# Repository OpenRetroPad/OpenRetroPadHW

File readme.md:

OpenRetroPad Hardware
=====================

This repository holds some hardware designs to support [OpenRetroPad](https://github.com/OpenRetroPad/OpenRetroPad) software development. For more information, see specific hardware directories.

* [ATmega32u4](ATmega32u4)

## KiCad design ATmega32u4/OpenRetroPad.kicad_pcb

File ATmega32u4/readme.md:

# OpenRetroPadHW - ATmega32u4

* [Schematic](outputs/OpenRetroPad.pdf)
* [Layout/Assembly](outputs/OpenRetroPad-Assembly.pdf)
* [PCB Top](outputs/OpenRetroPad-top.png)
* [PCB Bottom](outputs/OpenRetroPad-bottom.png)

## Overview

This board is based around an [ATmega32u4](https://www.microchip.com/en-us/product/ATmega32U4) which is commonly seen on the official [Arduino Micro](https://docs.arduino.cc/hardware/micro) and [Leonardo](https://docs.arduino.cc/hardware/leonardo) boards. They are also on a fair number of third party Arduino compatible boards known as 'Pro Micro' (e.g. sparkfun's [Pro Micro](https://www.sparkfun.com/products/12640)).

The current design includes two USB-C plugs of which both can be used for programming, J2 over a CH330N/CH340N USB-UART serial connection or J1 over USB DFU.

A 2x4 female 2.54mm/0.1in header is also available for an nRF24L01 wireless transceiver module.

Controllers can be connected via a male DB25 mounted on the PCB. The recommended way of doing this with off the shelf controllers is by splicing cheap extension cables with a DB25 connector.

The PCB has been designed to be manufactured and assembled with [JLCPCB](https://jlcpcb.com/). Cost was part of the decision to use this company, but also the easy integration with their sister company [LCSC](https://www.lcsc.com/) which makes the ordering process for the BOM relatively painless (providing you are using parts available in their library).

## Software

[KiCad](https://www.kicad.org/) was used to design the schematic and PCB. Version 6 has come leaps and bounds and is a very capable ecad software compared to commercial offerings.

The schematic uses a heirachical design and [vector buses](https://docs.kicad.org/6.0/en/eeschema/eeschema.html#bus-connections) extensively. To view the pins for each vector bus, select the _Tools_ -> _Bus Definitions_ menu in the schematic editor.

Output PNG files were generated using the following linux commands,
```
pdftoppm OpenRetroPad.pdf png/OpenRetroPad.pdf -png -r 600
pdftoppm OpenRetroPad-Assembly.pdf png/OpenRetroPad-Assembly.pdf -png -r 600
pngquant --ext .png -f --skip-if-larger --speed 1 --strip png/*.png
```

### Plugins

* [Board2Pdf](https://gitlab.com/dennevi/Board2Pdf) has been used to generate the assembly PDF from the PCB layers. COlours have been adjusted to roughly match the default KiCad 6 theme colours for copper, silkscreen etc.

* [KiCAD JLCPCB tools](https://github.com/bouni/kicad-jlcpcb-tools) has been used to simplify the part selection for the BOM and generate assembly outputs for the manufacturer.

## Hardware Design

#### Mechanical

M3 (3.2mm diameter) mounting holes have been added to the corner of the board. These holes have exposed copper for screws, but are not grounded. For precise measurements, see the assembly PDF above.

TODO:
* Consider grounding mounting hole pads

#### Power

The board is powered by either USB-C connector, which have been separated from each other, and provided with some basic reverse polarity protection, with a schottky diode on each VBUS connection. This will mean an approximate 0.3V drop on the 5V line but that should be more than fine for this purpose. The microcontroller still runs acceptably fine above 4.5V at 16MHz.

Assumptions have been made that the 5V USB supply is relatively stable so for the digital supply only decoupling capacitors are used. However, a ferrite bead has also been used for filtering the two analog supply inputs.

A larger 'bulk' 10u capacitor has been added near the each USB connector supply, and each CC pin has been pulled down with 5.1k resistors as per the USB spec Rd pulldown resistor for basic USB power. The CC pins have been routed to the microcontroller for the data connector to measure the voltage divider and power available.

A power LED is used on the 5V line. This LED can be physically disabled by cutting the JP1 solder bridge.

TODO:
* Test if both USB-C connectors can be used simultaneously with the schottky diodes
* Potentially add ferrite bead on each USB supply
* Fuses on inputs?
* Consider filter on USB shield - potentially small cap and large resistor, or even a ferrite bead

#### Microcontroller

The microcontroller was initially based on microchip application mate [AN2519 - AVR Microcontroller Hardware Design Considerations (DS00002519)](https://ww1.microchip.com/downloads/en/Appnotes/AN2519-AVR-Microcontroller-Hardware-Design-Considerations-00002519B.pdf).

The [quad flat package](https://en.wikipedia.org/wiki/Quad_flat_package) was used for this microcontroller, as opposed to the [quad flat no-lead package](https://en.wikipedia.org/wiki/Flat_no-leads_package). Throughout the covid chip shortage, the QFP part were harder to source and more expensive, but have now come back down to reasonable levels.

##### Programming via USB DFU

The board can be programmed via UART, but some information is provided here for programming via USB DFU if any issues are encountered.

Bootloader uses [PC7](https://github.com/arduino/ArduinoCore-avr/blob/master/bootloaders/caterina/Caterina.h#L69) as output for led pulsing in hardware bootloader mode ( https://github.com/arduino/ArduinoCore-avr/blob/master/bootloaders/caterina/Caterina.c#L151 and https://github.com/arduino/ArduinoCore-avr/blob/master/bootloaders/caterina/Caterina.c#L95 ). This LED can otherwise be used in user code for status indication. TX (D5) and RX (B0) are also broken out for LED activity.

Switch 1 (labelled 'HWB') enters hardware bootloader mode. Switch 2 (labelled 'Reset') resets the microcontroller. To enter the hardware bootloader, in this order: press reset, press hwb, release reset, release hwb. HWB has weak pullup to not use bootloader on reset.

USB DFU mode as per http://ww1.microchip.com/downloads/en/DeviceDoc/doc7618.pdf

DFU drivers can be found in [FLIP](https://www.microchip.com/developmenttools/ProductDetails/flip)
Flip is not required to be installed unless uploading a .hex file manually

Flags to avrdude to upload: -c flip1 -p m32u4 -P usb
Flip is not required to be installed for avrdude to use the protocol.

#### UART

The CH330N/CH340N are interchangeable parts. Datasheet recommends not powering CH340 and MCU separately. Could cause issues when using TX/RX port for controllers.

TODO:
* Investigate powering separately, adding diode instead of resistors to RXD/TXD

#### I/O

The DB-25 male connector is connected as per the [wiring table here](https://github.com/openRetroPad/openRetroPad#wiring)

The 5V and 3.3V lines are both fused for protection.

Once the microcontroller is booted (a few milliseconds), the HWB button can be used as a user programmable button.

There are multiple LEDs on the board that can be used for I/O.

#### Wireless Transceiver

The original software had functionality for wireless connections using an nRF24L01 module. This board provides a header to plug in one of these modules. They don't appear to be "official" nordic semi modules in any capacity, but any module with the pinout matching the header (check the back side of the PCB) should work.

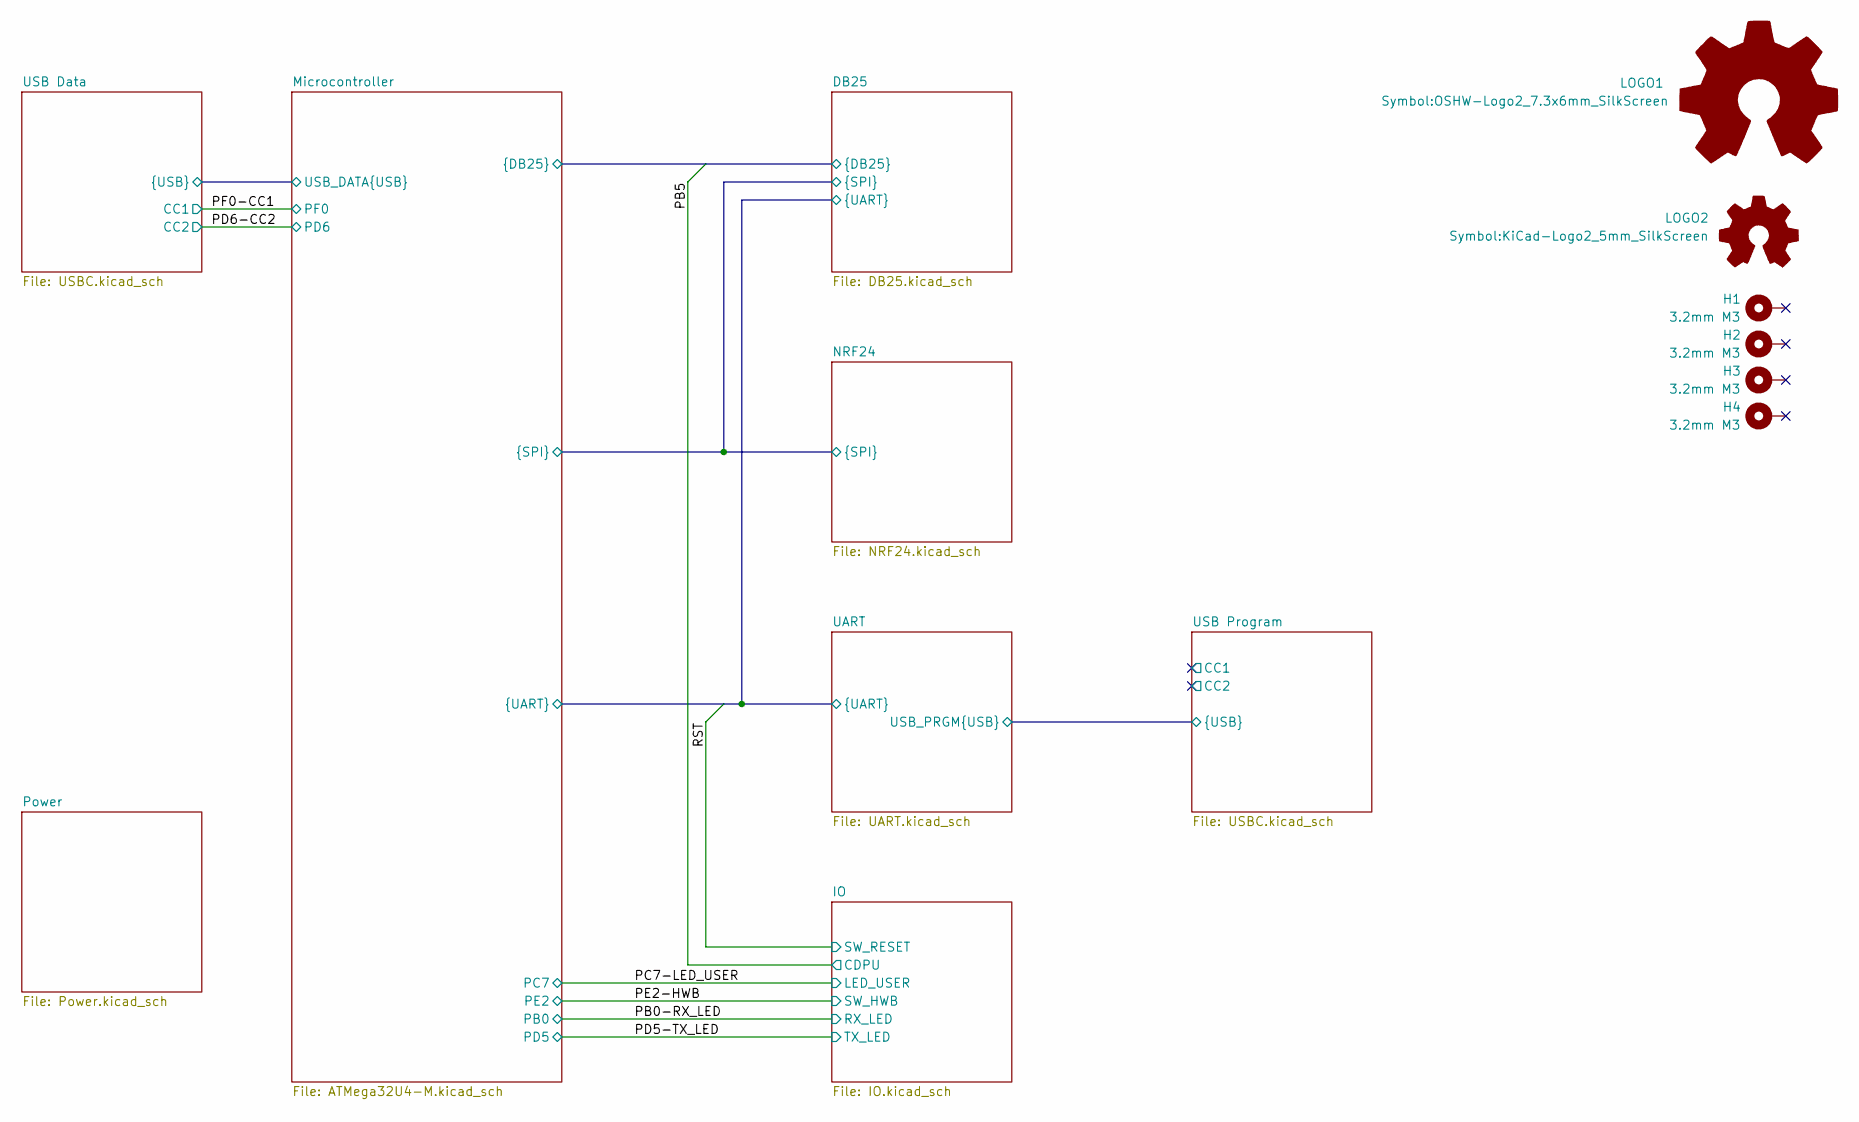
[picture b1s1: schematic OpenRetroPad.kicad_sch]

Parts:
H1, H2, H3, H4: 3.2mm M3; MountingHole_3.2mm_M3_Pad_Via
LOGO1: Logo_Open_Hardware_Large; OSHW-Logo2_7.3x6mm_SilkScreen
LOGO2: Logo_Open_Hardware_Small; KiCad-Logo2_5mm_SilkScreen

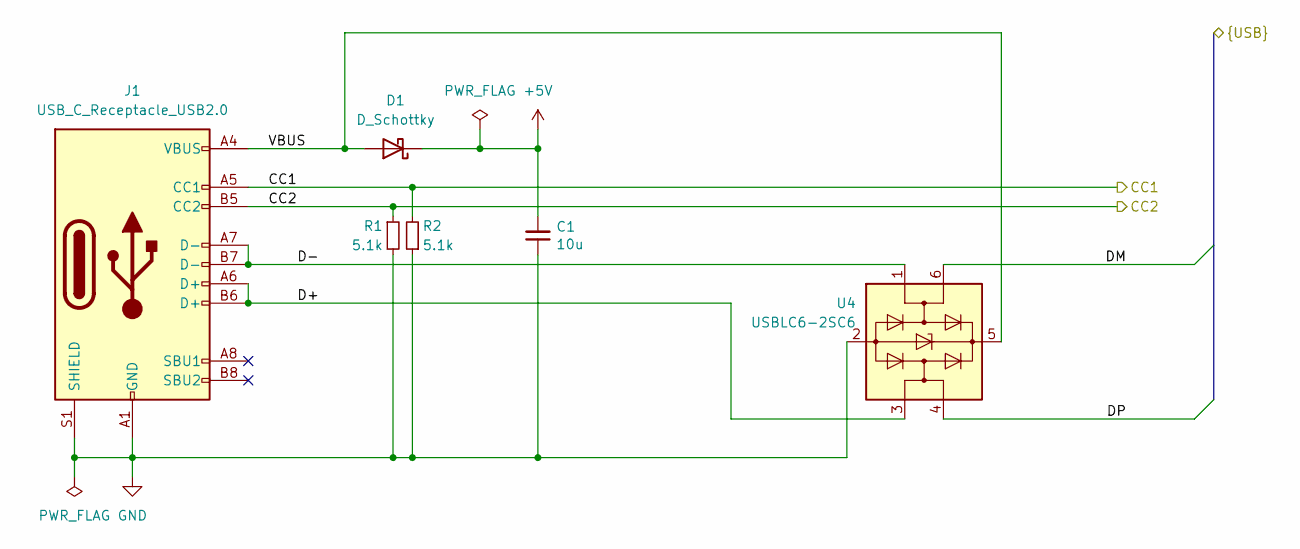
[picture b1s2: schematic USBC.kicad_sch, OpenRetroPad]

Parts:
C1: 10u; C_0805_2012Metric
D1: D_Schottky; D_SOD-323
J1: USB_C_Receptacle_USB2.0; USB_C_Receptacle_HRO_TYPE-C-31-M-12
R1, R2: 5.1k; R_0603_1608Metric
U4: USBLC6-2SC6; SOT-23-6

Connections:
+5V: C1.2, D1.1 (K); also elsewhere on the board
/Microcontroller/USB_DATA.DM: U4.6 (I/O1); also elsewhere on the board
/Microcontroller/USB_DATA.DP: U4.4 (I/O2); also elsewhere on the board
/PD6-CC2: J1.B5 (CC2), R1.1; also elsewhere on the board
/PF0-CC1: J1.A5 (CC1), R2.2; also elsewhere on the board
/USB Data/D+: J1.A6 (D+), J1.B6 (D+), U4.3 (I/O2)
/USB Data/D-: J1.A7 (D-), J1.B7 (D-), U4.1 (I/O1)
/USB Data/VBUS: D1.2 (A), J1.A4 (VBUS), J1.A9 (VBUS), J1.B4 (VBUS), J1.B9 (VBUS), U4.5 (VBUS)
GND: C1.1, J1.A1 (GND), J1.A12 (GND), J1.B1 (GND), J1.B12 (GND), J1.S1 (SHIELD), R1.2, R2.1, U4.2 (GND); also elsewhere on the board

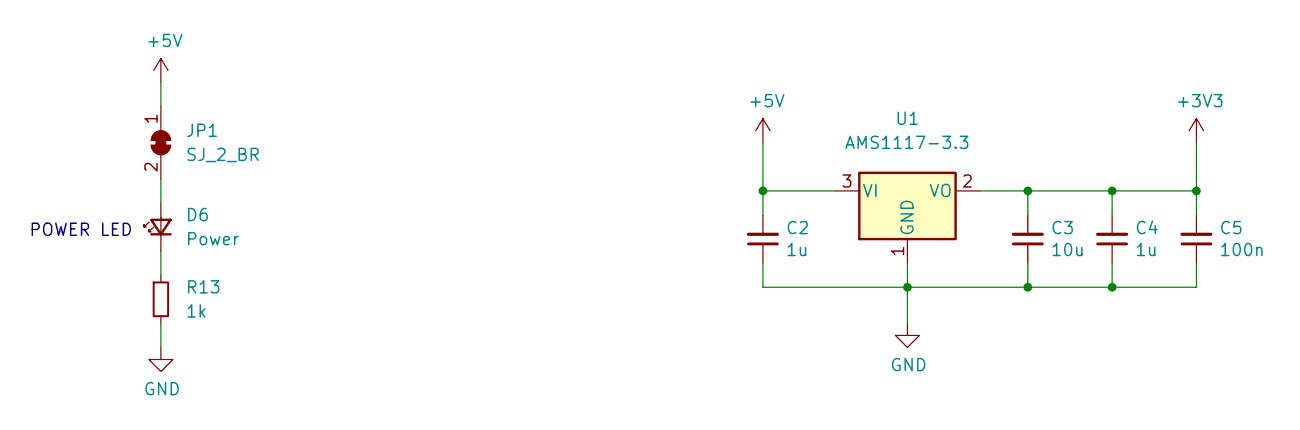
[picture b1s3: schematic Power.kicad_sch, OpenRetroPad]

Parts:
C2, C4: 1u; C_0603_1608Metric
C3: 10u; C_0805_2012Metric
C5: 100n; C_0603_1608Metric
D6: Power; LED_0603_1608Metric
JP1: SJ_2_BR; SolderJumper-2_P1.3mm_Bridged_RoundedPad1.0x1.5mm
R13: 1k; R_0603_1608Metric
U1: AMS1117-3.3; SOT-223-3_TabPin2

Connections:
+3V3: C3.2, C4.2, C5.2, U1.2 (VO); also elsewhere on the board
+5V: C2.2, JP1.1 (A), U1.3 (VI); also elsewhere on the board
GND: C2.1, C3.1, C4.1, C5.1, R13.2, U1.1 (GND); also elsewhere on the board
unnamed: D6.1 (K), R13.1
unnamed: D6.2 (A), JP1.2 (B)

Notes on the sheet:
POWER LED

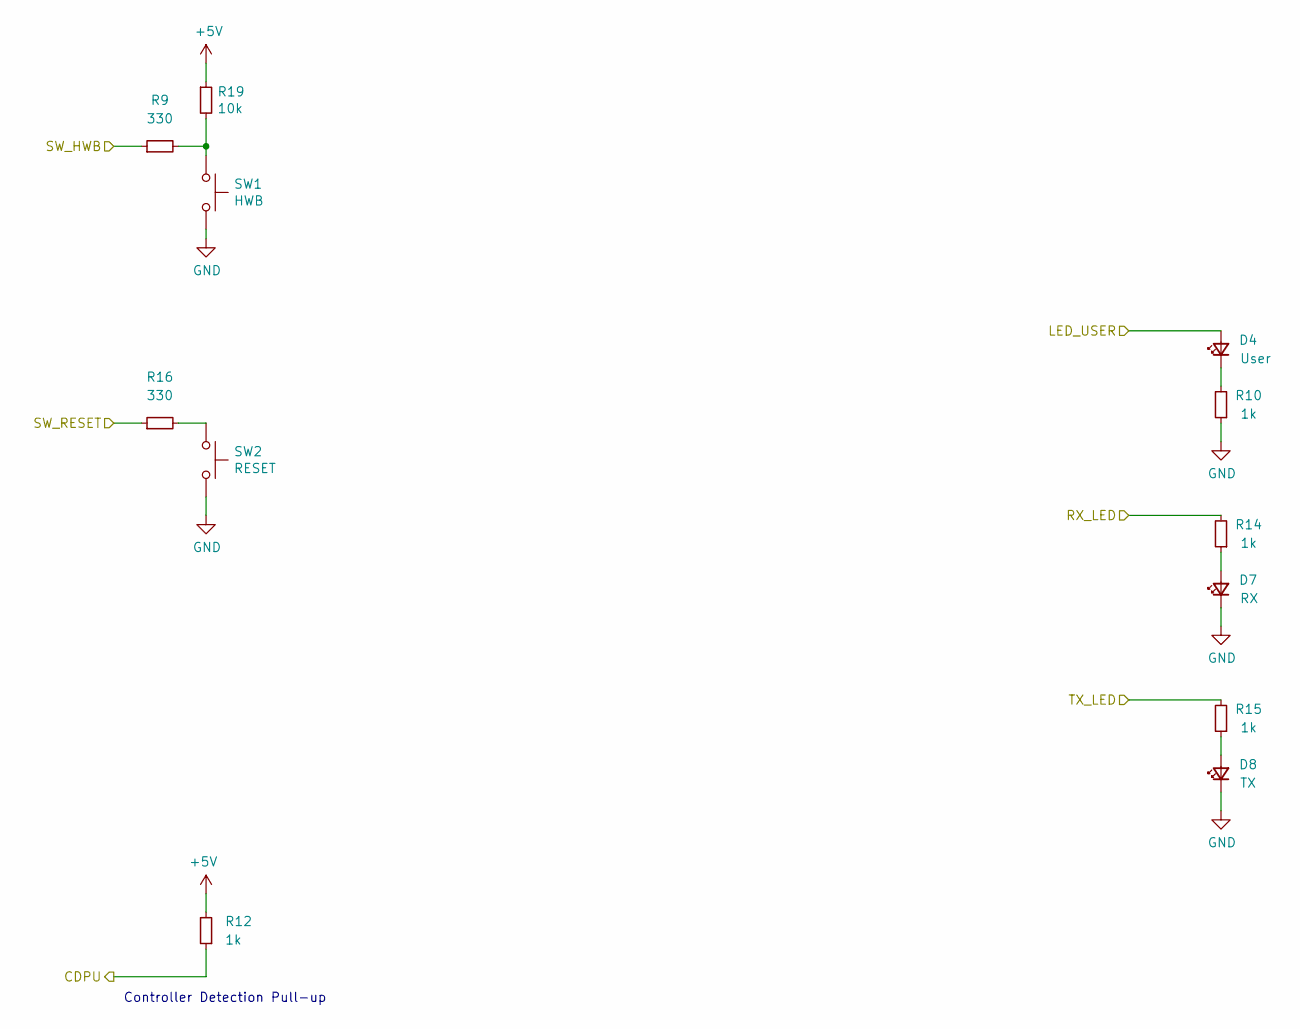
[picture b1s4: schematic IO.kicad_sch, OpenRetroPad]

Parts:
D4: User; LED_0603_1608Metric
D7: RX; LED_0603_1608Metric
D8: TX; LED_0603_1608Metric
R9, R16: 330; R_0603_1608Metric
R10, R12, R14, R15: 1k; R_0603_1608Metric
R19: 10k; R_0603_1608Metric
SW1: HWB; Alps_SKRK
SW2: RESET; Alps_SKRK

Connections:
+5V: R12.2, R19.1; also elsewhere on the board
/DB25/PB5: R12.1; also elsewhere on the board
/DB25/RST: R16.1; also elsewhere on the board
/PB0-RX_LED: R14.2; also elsewhere on the board
/PC7-LED_USER: D4.2 (A); also elsewhere on the board
/PD5-TX_LED: R15.2; also elsewhere on the board
/PE2-HWB: R9.1; also elsewhere on the board
GND: D7.1 (K), D8.1 (K), R10.1, SW1.2, SW2.2; also elsewhere on the board
unnamed: D4.1 (K), R10.2
unnamed: D7.2 (A), R14.1
unnamed: D8.2 (A), R15.1
unnamed: R16.2, SW2.1
unnamed: R9.2, R19.2, SW1.1

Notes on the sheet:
Controller Detection Pull-up

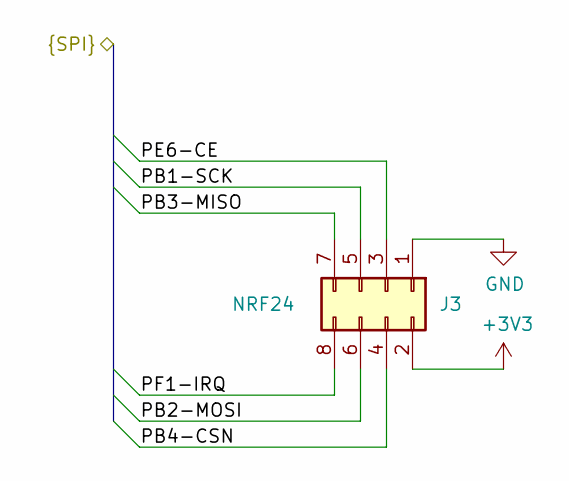
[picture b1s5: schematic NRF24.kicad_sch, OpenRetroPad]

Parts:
J3: NRF24; NRF24L01

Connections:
+3V3: J3.2; also elsewhere on the board
/DB25/PB1-SCK: J3.5; also elsewhere on the board
/DB25/PB2-MOSI: J3.6; also elsewhere on the board
/DB25/PB3-MISO: J3.7; also elsewhere on the board
/DB25/PB4-CSN: J3.4; also elsewhere on the board
/DB25/PE6-CE: J3.3; also elsewhere on the board
/DB25/PF1-IRQ: J3.8; also elsewhere on the board
GND: J3.1; also elsewhere on the board

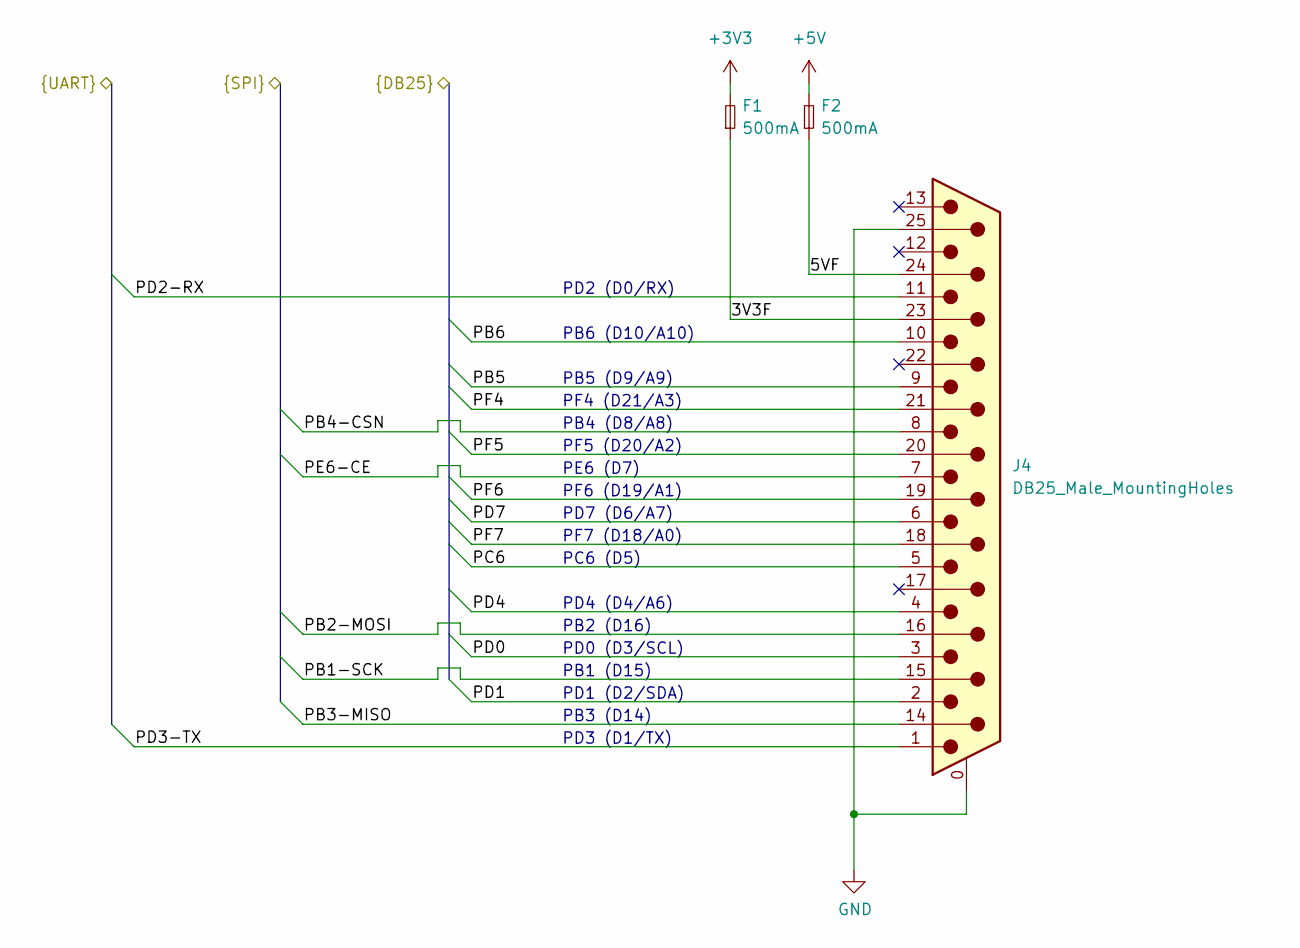
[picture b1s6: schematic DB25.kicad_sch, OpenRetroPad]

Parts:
F1, F2: 500mA; Fuse_0805_2012Metric
J4: DB25_Male_MountingHoles; DSUB-25_Male_Horizontal_P2.77x2.84mm_EdgePinOffset7.70mm_Ho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

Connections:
+3V3: F1.2; also elsewhere on the board
+5V: F2.2; also elsewhere on the board
/DB25/3V3F: F1.1, J4.23
/DB25/5VF: F2.1, J4.24
/DB25/PB1-SCK: J4.15; also elsewhere on the board
/DB25/PB2-MOSI: J4.16; also elsewhere on the board
/DB25/PB3-MISO: J4.14; also elsewhere on the board
/DB25/PB4-CSN: J4.8; also elsewhere on the board
/DB25/PB5: J4.9; also elsewhere on the board
/DB25/PB6: J4.10; also elsewhere on the board
/DB25/PC6: J4.5; also elsewhere on the board
/DB25/PD0: J4.3; also elsewhere on the board
/DB25/PD1: J4.2; also elsewhere on the board
/DB25/PD2-RX: J4.11; also elsewhere on the board
/DB25/PD3-TX: J4.1; also elsewhere on the board
/DB25/PD4: J4.4; also elsewhere on the board
/DB25/PD7: J4.6; also elsewhere on the board
/DB25/PE6-CE: J4.7; also elsewhere on the board
/DB25/PF4: J4.21; also elsewhere on the board
/DB25/PF5: J4.20; also elsewhere on the board
/DB25/PF6: J4.19; also elsewhere on the board
/DB25/PF7: J4.18; also elsewhere on the board
GND: J4.0 (PAD), J4.25; also elsewhere on the board

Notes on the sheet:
PD2 (D0/RX)
PD0 (D3/SCL)
PD4 (D4/A6)
PF6 (D19/A1)
PF4 (D21/A3)
PC6 (D5)
PB4 (D8/A8)
PB1 (D15)
PE6 (D7)
PB5 (D9/A9)
PD1 (D2/SDA)
PD3 (D1/TX)
PB3 (D14)
PF7 (D18/A0)
PB2 (D16)
PD7 (D6/A7)
PB6 (D10/A10)
PF5 (D20/A2)

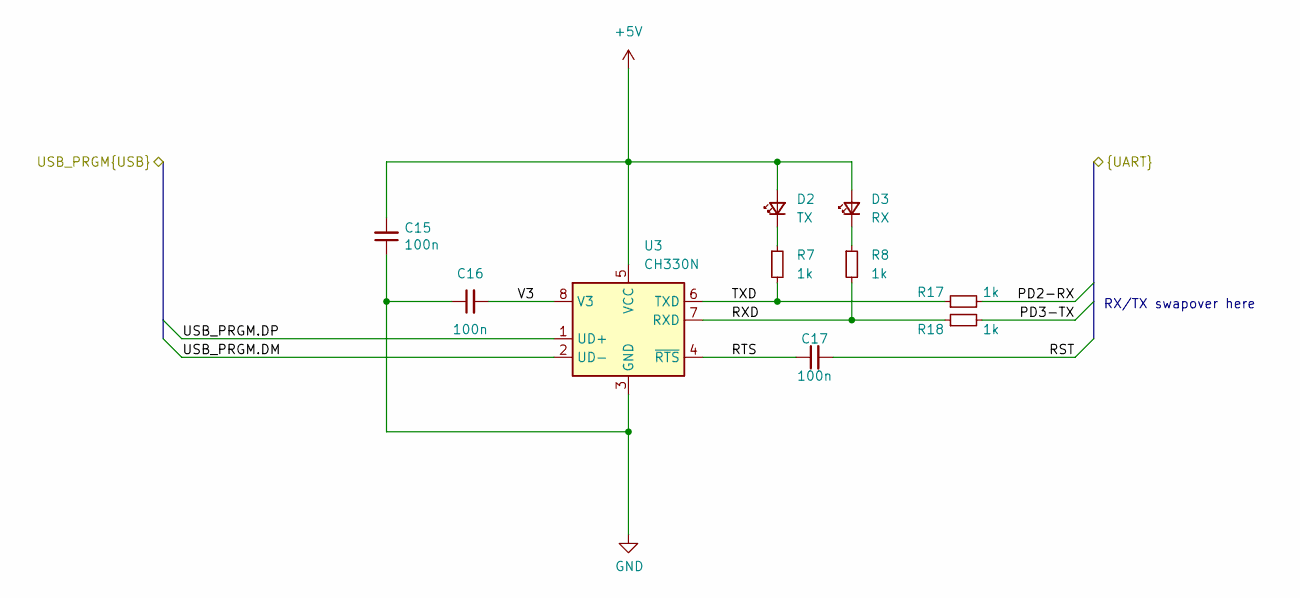
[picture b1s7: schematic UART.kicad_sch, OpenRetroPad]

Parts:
C15, C16, C17: 100n; C_0603_1608Metric
D2: TX; LED_0603_1608Metric
D3: RX; LED_0603_1608Metric
R7, R8, R17, R18: 1k; R_0603_1608Metric
U3: CH330N; SOIC-8_3.9x4.9mm_P1.27mm

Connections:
+5V: C15.2, D2.2 (A), D3.2 (A), U3.5 (VCC); also elsewhere on the board
/DB25/PD2-RX: R17.2; also elsewhere on the board
/DB25/PD3-TX: R18.2; also elsewhere on the board
/DB25/RST: C17.2; also elsewhere on the board
/UART/RTS: C17.1, U3.4 (~RTS)
/UART/RXD: R8.2, R18.1, U3.7 (RXD)
/UART/TXD: R7.2, R17.1, U3.6 (TXD)
/UART/USB_PRGM.DM: U3.2 (UD-); also elsewhere on the board
/UART/USB_PRGM.DP: U3.1 (UD+); also elsewhere on the board
/UART/V3: C16.2, U3.8 (V3)
GND: C15.1, C16.1, U3.3 (GND); also elsewhere on the board
unnamed: D2.1 (K), R7.1
unnamed: D3.1 (K), R8.1

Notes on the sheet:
RX/TX swapover here

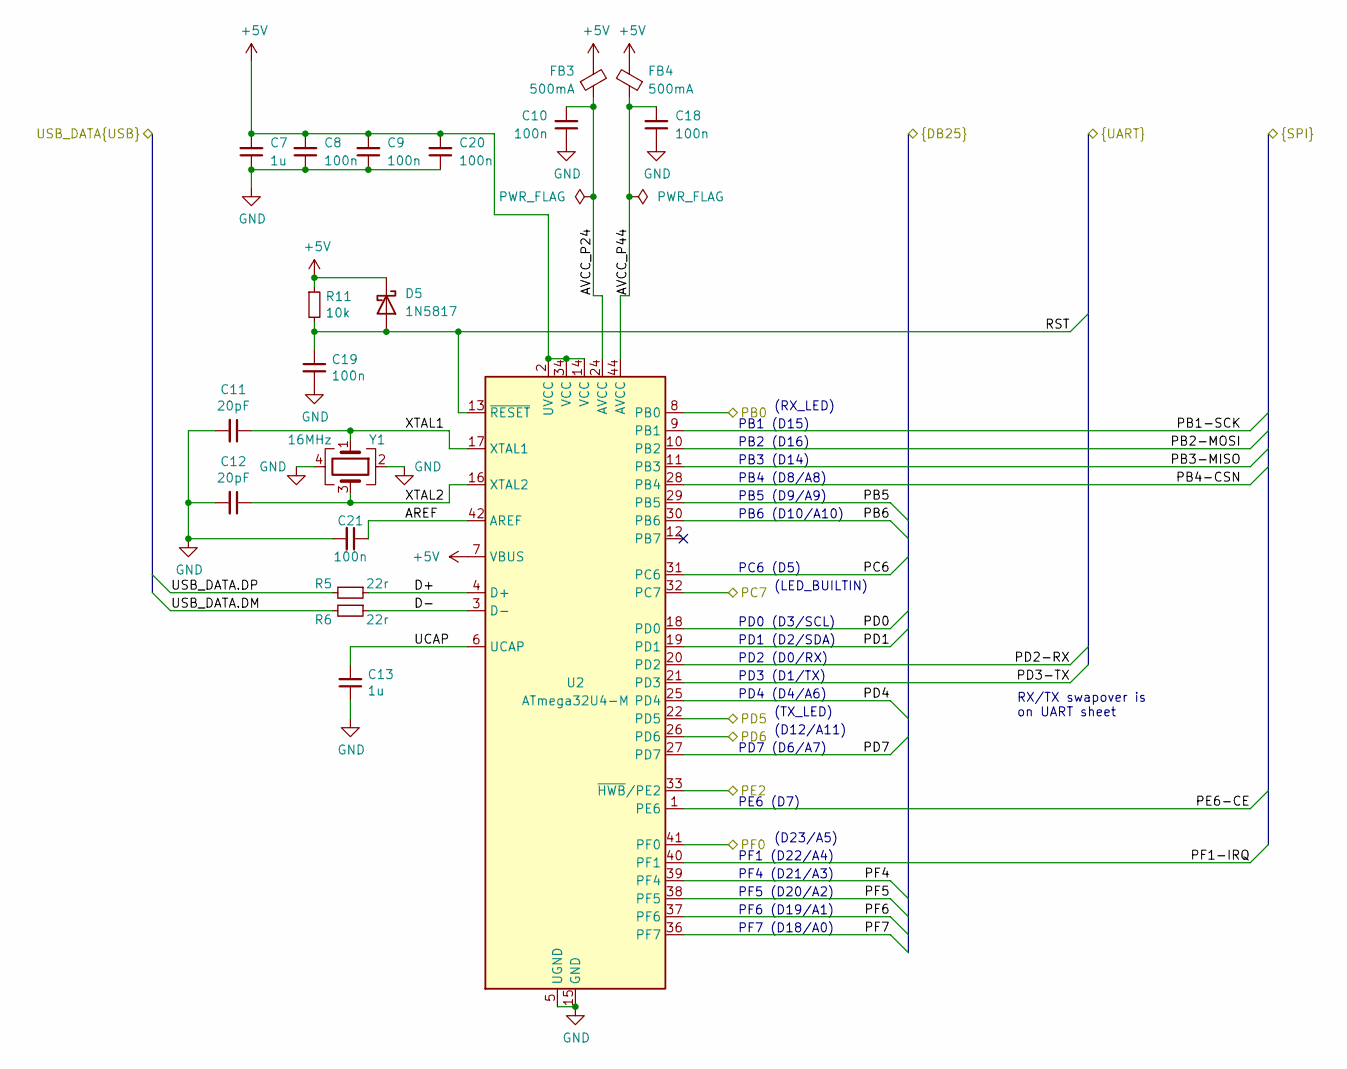
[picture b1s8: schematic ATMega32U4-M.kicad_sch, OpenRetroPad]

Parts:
C7, C13: 1u; C_0603_1608Metric
C8, C9, C10, C18, C19, C20, C21: 100n; C_0603_1608Metric
C11, C12: 20pF; C_0603_1608Metric
D5: 1N5817; D_SOD-323
FB3, FB4: 500mA; L_0603_1608Metric
R5, R6: 22r; R_0603_1608Metric
R11: 10k; R_0603_1608Metric
U2: ATmega32U4-M; TQFP-44_10x10mm_P0.8mm
Y1: 16MHz; Crystal_SMD_3225-4Pin_3.2x2.5mm

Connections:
+5V: C7.2, C8.2, C9.2, C20.2, D5.1 (K), FB3.2, FB4.2, R11.1, U2.2 (UVCC), U2.7 (VBUS), U2.14 (VCC), U2.34 (VCC); also elsewhere on the board
/DB25/PB1-SCK: U2.9 (PB1); also elsewhere on the board
/DB25/PB2-MOSI: U2.10 (PB2); also elsewhere on the board
/DB25/PB3-MISO: U2.11 (PB3); also elsewhere on the board
/DB25/PB4-CSN: U2.28 (PB4); also elsewhere on the board
/DB25/PB5: U2.29 (PB5); also elsewhere on the board
/DB25/PB6: U2.30 (PB6); also elsewhere on the board
/DB25/PC6: U2.31 (PC6); also elsewhere on the board
/DB25/PD0: U2.18 (PD0); also elsewhere on the board
/DB25/PD1: U2.19 (PD1); also elsewhere on the board
/DB25/PD2-RX: U2.20 (PD2); also elsewhere on the board
/DB25/PD3-TX: U2.21 (PD3); also elsewhere on the board
/DB25/PD4: U2.25 (PD4); also elsewhere on the board
/DB25/PD7: U2.27 (PD7); also elsewhere on the board
/DB25/PE6-CE: U2.1 (PE6); also elsewhere on the board
/DB25/PF1-IRQ: U2.40 (PF1); also elsewhere on the board
/DB25/PF4: U2.39 (PF4); also elsewhere on the board
/DB25/PF5: U2.38 (PF5); also elsewhere on the board
/DB25/PF6: U2.37 (PF6); also elsewhere on the board
/DB25/PF7: U2.36 (PF7); also elsewhere on the board
/DB25/RST: C19.1, D5.2 (A), R11.2, U2.13 (~RESET); also elsewhere on the board
/Microcontroller/AREF: C21.1, U2.42 (AREF)
/Microcontroller/AVCC_P24: C10.2, FB3.1, U2.24 (AVCC)
/Microcontroller/AVCC_P44: C18.2, FB4.1, U2.44 (AVCC)
/Microcontroller/D+: R5.1, U2.4 (D+)
/Microcontroller/D-: R6.1, U2.3 (D-)
/Microcontroller/UCAP: C13.2, U2.6 (UCAP)
/Microcontroller/USB_DATA.DM: R6.2; also elsewhere on the board
/Microcontroller/USB_DATA.DP: R5.2; also elsewhere on the board
/Microcontroller/XTAL1: C11.1, U2.17 (XTAL1), Y1.1
/Microcontroller/XTAL2: C12.1, U2.16 (XTAL2), Y1.3
/PB0-RX_LED: U2.8 (PB0); also elsewhere on the board
/PC7-LED_USER: U2.32 (PC7); also elsewhere on the board
/PD5-TX_LED: U2.22 (PD5); also elsewhere on the board
/PD6-CC2: U2.26 (PD6); also elsewhere on the board
/PE2-HWB: U2.33 (~HWB/PE2); also elsewhere on the board
/PF0-CC1: U2.41 (PF0); also elsewhere on the board
GND: C7.1, C8.1, C9.1, C10.1, C11.2, C12.2, C13.1, C18.1, C19.2, C20.1, C21.2, U2.5 (UGND), U2.15 (GND), U2.23 (GND), U2.35 (GND), U2.43 (GND), Y1.2, Y1.4; also elsewhere on the board

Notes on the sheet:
PD4 (D4/A6)
PD3 (D1/TX)
PD0 (D3/SCL)
(D23/A5)
PB6 (D10/A10)
PD1 (D2/SDA)
(D12/A11)
PB1 (D15)
RX/TX swapover is on UART sheet
PB3 (D14)
(LED_BUILTIN)
PF1 (D22/A4)
PB2 (D16)
PE6 (D7)
PD7 (D6/A7)
(RX_LED)
PF6 (D19/A1)
PF5 (D20/A2)
PF4 (D21/A3)
PB4 (D8/A8)
PB5 (D9/A9)
PC6 (D5)
PF7 (D18/A0)
PD2 (D0/RX)
(TX_LED)

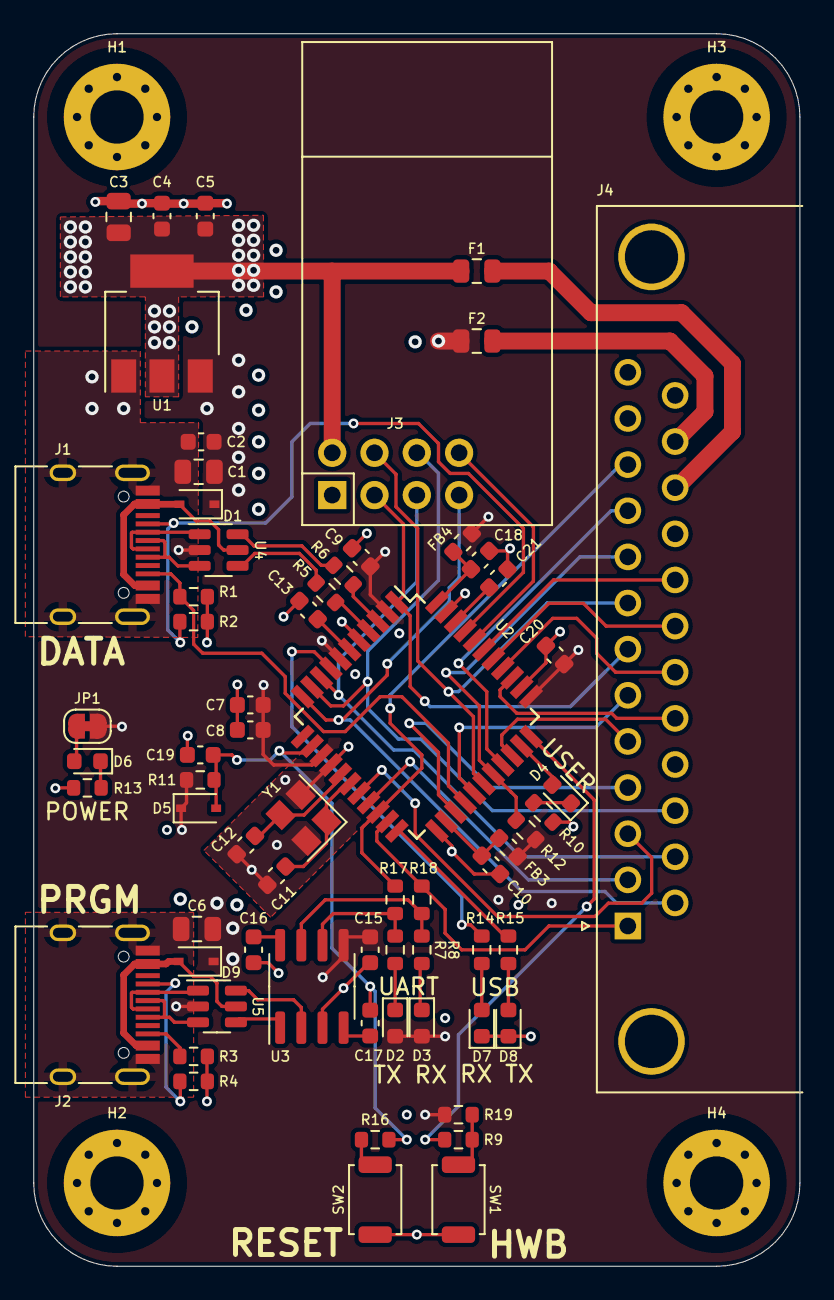
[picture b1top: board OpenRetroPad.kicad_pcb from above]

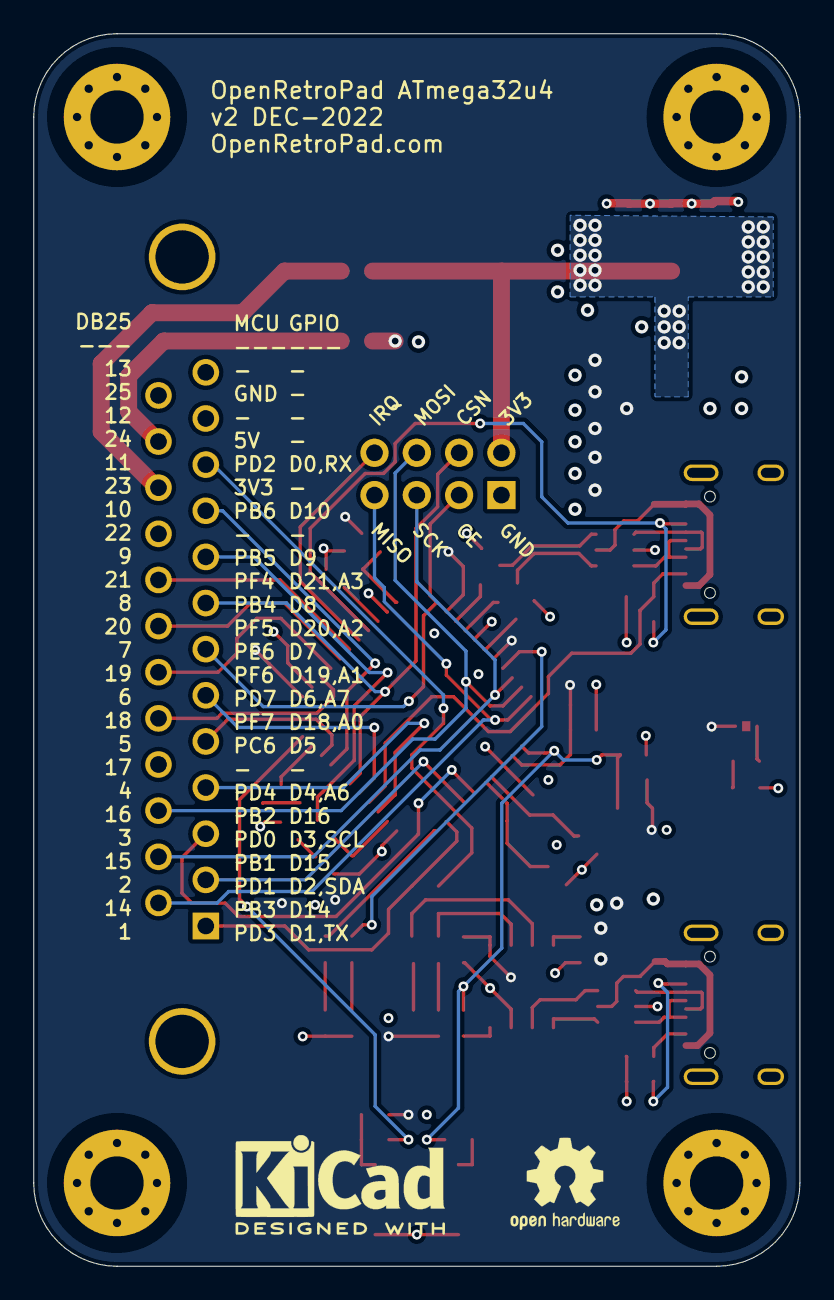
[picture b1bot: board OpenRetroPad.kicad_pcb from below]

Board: 4 copper layers, 46.0 x 74.0 mm, 71 parts (2 on the bottom side), 64 nets.

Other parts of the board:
C6: 10u; C_0805_2012Metric
D9: D_Schottky; D_SOD-323
J2: USB_C_Receptacle_USB2.0; USB_C_Receptacle_HRO_TYPE-C-31-M-12
R3, R4: 5.1k; R_0603_1608Metric
U5: USBLC6-2SC6; SOT-23-6

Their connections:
+5V: C6.2, D9.1 (K); also elsewhere on the board
/UART/USB_PRGM.DM: U5.6 (I/O1); also elsewhere on the board
/UART/USB_PRGM.DP: U5.4 (I/O2); also elsewhere on the board
/USB Program/CC1: J2.A5 (CC1), R4.2
/USB Program/CC2: J2.B5 (CC2), R3.1
/USB Program/D+: J2.A6 (D+), J2.B6 (D+), U5.3 (I/O2)
/USB Program/D-: J2.A7 (D-), J2.B7 (D-), U5.1 (I/O1)
/USB Program/VBUS: D9.2 (A), J2.A4 (VBUS), J2.A9 (VBUS), J2.B4 (VBUS), J2.B9 (VBUS), U5.5 (VBUS)
GND: C6.1, J2.A1 (GND), J2.A12 (GND), J2.B1 (GND), J2.B12 (GND), J2.S1 (SHIELD), R3.2, R4.1, U5.2 (GND); also elsewhere on the board

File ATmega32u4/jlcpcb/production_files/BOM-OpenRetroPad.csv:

Comment,Designator,Footprint,LCSC
500mA,"FB3,FB4",L_0603_1608Metric,C1002
HWB,"SW1,SW2",Alps_SKRK,C115357
16MHz,Y1,Crystal_SMD_3225-4Pin_3.2x2.5mm,C13738
100n,"C10,C15,C16,C17,C18,C19,C20,C21,C5,C8,C9",C_0603_1608Metric,C14663
1u,"C13,C2,C4,C7",C_0603_1608Metric,C15849
10u,"C1,C3,C6",C_0805_2012Metric,C15850
20pF,"C11,C12",C_0603_1608Metric,C1648
USB_C_Receptacle_USB2.0,"J1,J2",USB_C_Receptacle_HRO_TYPE-C-31-M-12,C165948
D_Schottky,"D1,D5,D9",D_SOD-323,C191023
1k,"R10,R12,R13,R14,R15,R17,R18,R7,R8",R_0603_1608Metric,C21190
Power,D6,LED_0603_1608Metric,C2286
330,"R16,R9",R_0603_1608Metric,C23137
5.1k,"R1,R2,R3,R4",R_0603_1608Metric,C23186
22r,"R5,R6",R_0603_1608Metric,C23345
10k,"R11,R19",R_0603_1608Metric,C25804
500mA,"F1,F2",Fuse_0805_2012Metric,C269104
USBLC6-2SC6,"U4,U5",SOT-23-6,C2827654
CH330N,U3,SOIC-8_3.9x4.9mm_P1.27mm,C2977777
ATmega32U4-M,U2,TQFP-44_10x10mm_P0.8mm,C44854
AMS1117-3.3,U1,SOT-223-3_TabPin2,C6186
RX,"D3,D7",LED_0603_1608Metric,C72038
User,D4,LED_0603_1608Metric,C72041
TX,"D2,D8",LED_0603_1608Metric,C72043
DB25_Male_MountingHoles,J4,DSUB-25_Male_Horizontal_P2.77x2.84mm_EdgePinOffset7.70mm_Housed_MountingHolesOffset9.12mm,C75751
NRF24,J3,NRF24L01,C92271

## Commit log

2021-01-03 Initial ATmega32u4 hardware files
2021-01-03 Update layout around MicroUSB connector, add teardrops
2021-01-03 Update text on back to include domain name instead of github link
2021-01-06 Convert from 4 layer to 2 layer board
2021-01-06 Update outputs for 2 layer board
2021-01-24 Update 2 layer board and use 0805 components, include outputs
2021-01-24 Start updating readme with basic info, add images
2021-05-12 - Add on-board programmer - Micro USB -> USB-C
2022-12-11 Update V2
2022-12-11 Update layout/assembly pdf
2022-12-20 Review and updates to power path
2022-12-29 Schematic, routing and layout changes post review.
2022-12-29 Update notes, add io for reading cc pins, minor changes to schematic and routing.
2022-12-29 Update readme.md
    Fix links.
2023-01-05 Add pngs for schematic and assembly from pdfs
2023-01-09 Adjust copper pours on top/bottom layers, update assembly pdf to include inner layers
2023-01-09 Change CC pin <-> ADC pin, adjust routing
2023-01-09 Include measurements on assembly pdf
